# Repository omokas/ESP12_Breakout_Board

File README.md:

# ESP12_Breakout_Board
A breakout board for ESP12x boards designed for my thesis on HMU

ESP12x is a low cost WiFi module containing a ESP8266 microcontroller

Compatible with ESP12F and ESP12E modules from Espressif

# Credits
Orestis Mokas - PCB Design

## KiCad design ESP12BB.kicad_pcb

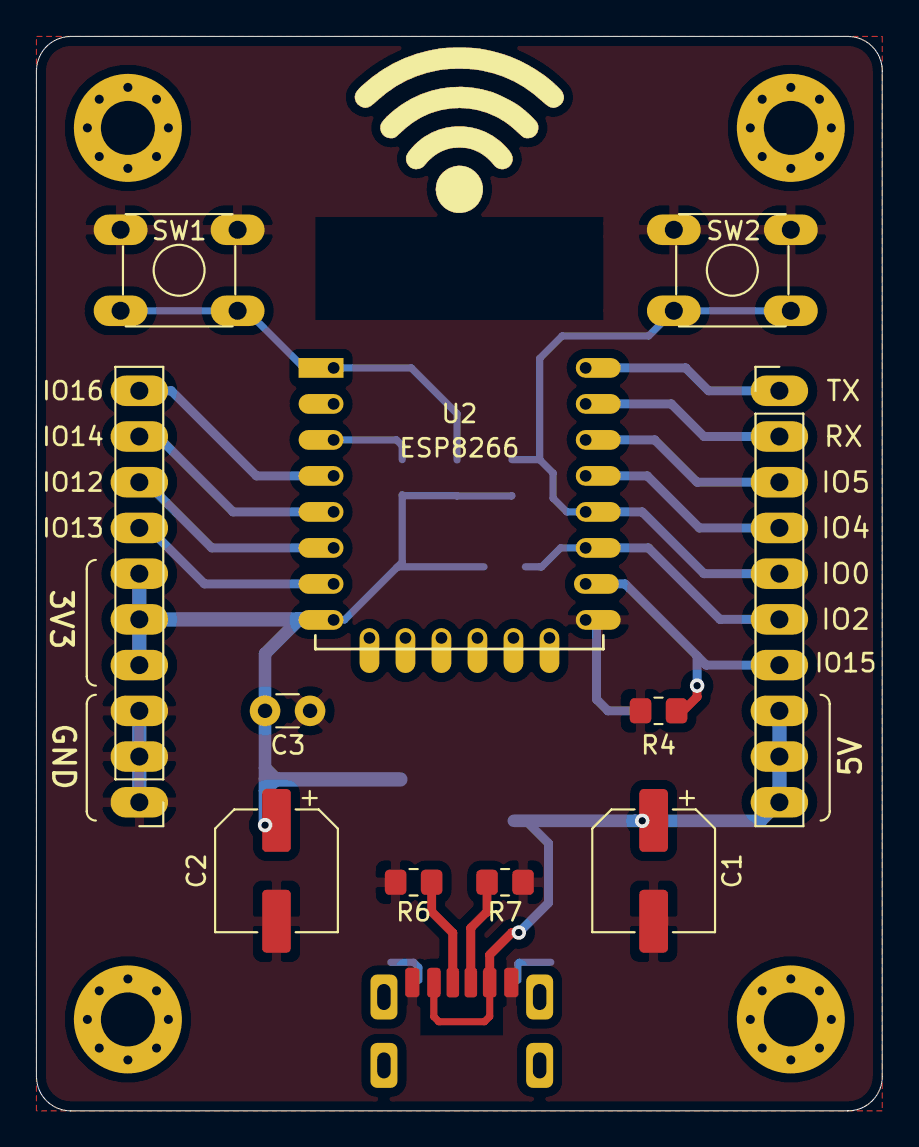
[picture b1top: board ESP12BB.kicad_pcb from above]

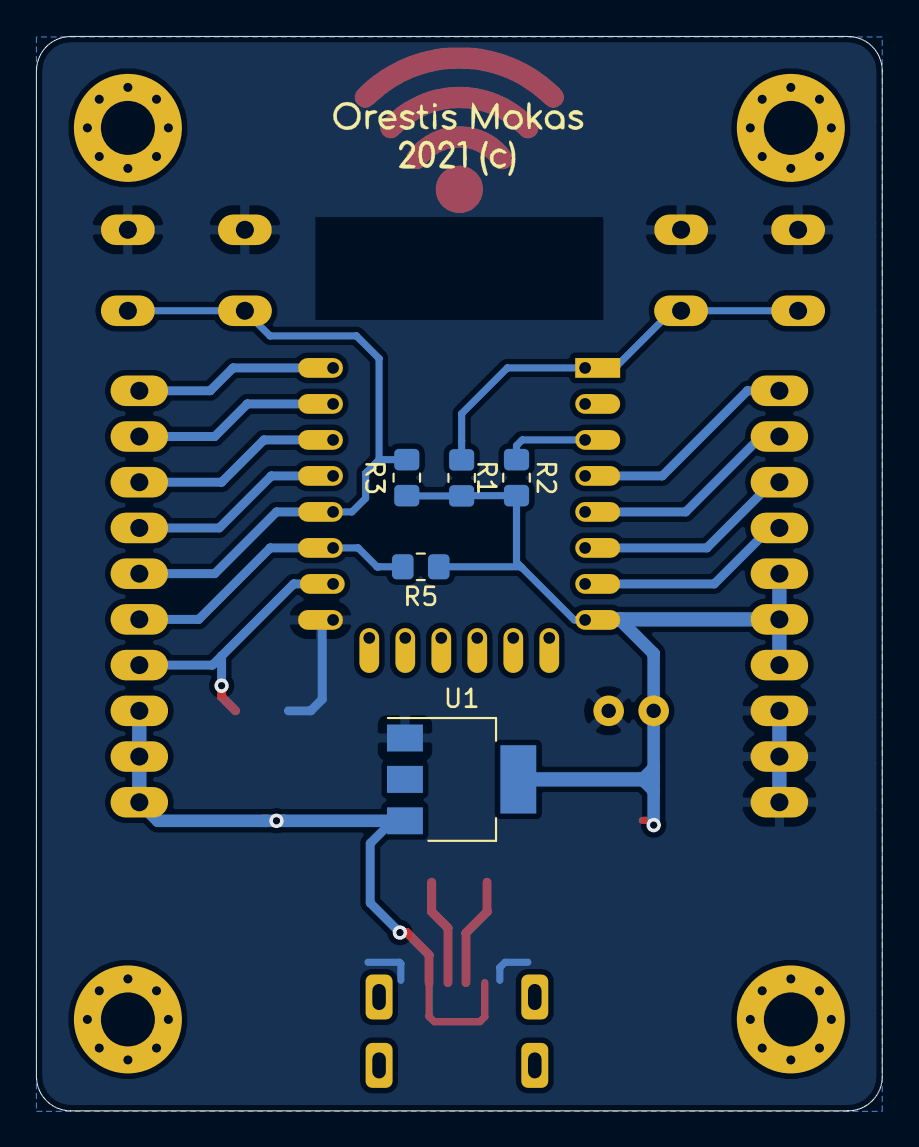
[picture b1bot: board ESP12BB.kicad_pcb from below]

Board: 2 copper layers, 47.0 x 59.7 mm, 17 parts (5 on the bottom side), 18 nets.

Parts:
C1, C2: 100uF; CP_Elec_6.3x5.3
C3: 100nF; C_Disc_D3.0mm_W1.6mm_P2.50mm
CONN1: USB_C; TypeC_6PIN
J1, J2: Conn_01x10; PinHeader_1x10_P2.54mm_Vertical
R1, R2, R3, R4, R5: 10K; R_0805_2012Metric_Pad1.20x1.40mm_HandSolder
R6, R7: 5.1K; R_0805_2012Metric_Pad1.20x1.40mm_HandSolder
SW1: RST_BTN; SW_TH_Tactile_Omron_B3F-10xx
SW2: PGR_BTN; SW_TH_Tactile_Omron_B3F-10xx
U1: LM1117-3.3; SOT-223-3_TabPin2
U2: ESP-12F; ESP-12E

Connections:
+3V3: C2.1, C3.1, J2.4, J2.5, J2.6, R1.2, R2.1, R3.1, R5.1, U1.2, U2.8
+5V: C1.1, CONN1.A9, CONN1.B9, J1.8, J1.9, J1.10, U1.3
GND: C1.2, C2.2, C3.2, CONN1.A12, CONN1.B12, J2.1, J2.2, J2.3, R4.2, R6.2, R7.1, SW1.2, SW1.4, SW2.2, SW2.4, U1.1, U2.9
IO0: J1.5, R3.2, SW2.1, SW2.3, U2.12
IO2: J1.6, R5.2, U2.11
IO4: J1.4, U2.13
IO5: J1.3, U2.14
IO12: J2.8, U2.6
IO13: J2.7, U2.7
IO14: J2.9, U2.5
IO15: J1.7, R4.1, U2.10
IO16: J2.10, U2.4
unnamed: CONN1.A5, R6.1
unnamed: CONN1.B5, R7.2
unnamed: R1.1, SW1.1, SW1.3, U2.1
unnamed: R2.2, U2.3
RX: J1.2, U2.15
TX: J1.1, U2.16

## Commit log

2025-09-28 Add KiCad files
